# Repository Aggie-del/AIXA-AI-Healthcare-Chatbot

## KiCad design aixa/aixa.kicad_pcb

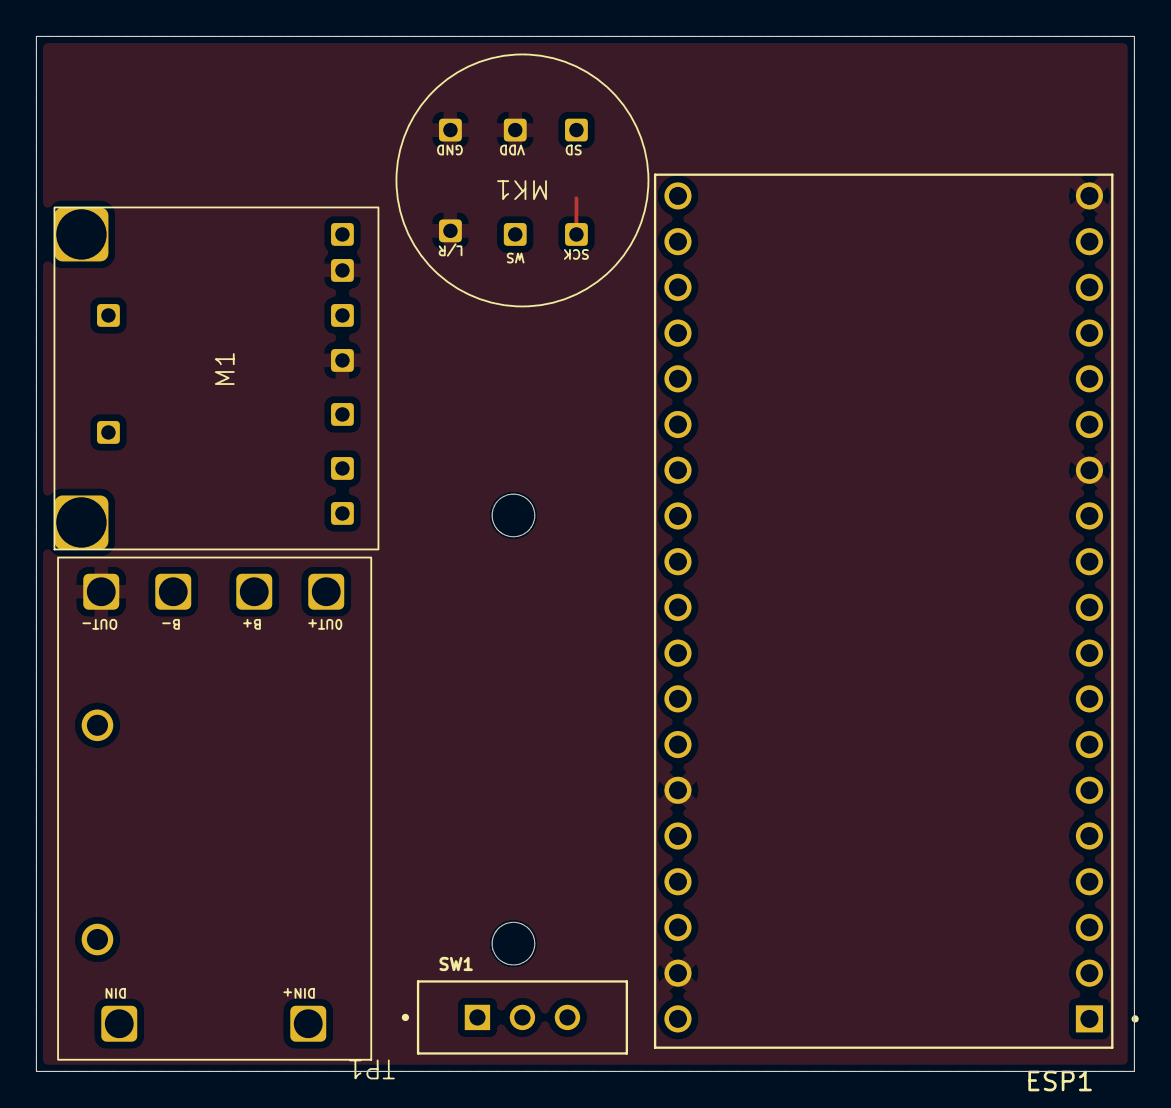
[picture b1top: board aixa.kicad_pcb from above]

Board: 2 copper layers, 61.0 x 57.5 mm, 6 parts (1 on the bottom side), 10 nets.

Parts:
BAT1: Battery; BAT_BC3AAAPC
ESP1: ESP32-S2-DEVKITM-1U; XCVR_ESP32-S2-DEVKITM-1U
M1: MAX98357A
MK1: INMP441ACEZ-R7; INMP4
SW1: SW_SPDT; SW_MINI-SPDT-SW
TP1: TP4056

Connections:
/BCLK: ESP1.17 (P22), M1.2 (BCLK), MK1.1 (SCK)
/DATA IN: ESP1.28 (P25), M1.3 (DIN)
/LRC: ESP1.29 (P26), M1.1 (LRC), MK1.3 (WS)
/SD: ESP1.26 (P32), MK1.2 (SD)
/SDOUT: ESP1.27 (P33), M1.5 (SD)
GND: ESP1.13 (GND), ESP1.19 (GND), ESP1.33 (GND), ESP1.37 (GND), M1.4 (GAIN), M1.6 (GND), MK1.4 (L/R), MK1.5 (GND), MK1.6 (GND), TP1.6 (OUT-)
unnamed: BAT1.1 (+), TP1.4 (B+)
unnamed: BAT1.2 (-), TP1.5 (B-)
unnamed: ESP1.38 (5V), M1.7 (VIN), SW1.2 (C)
unnamed: SW1.1 (B), TP1.3 (OUT+)
